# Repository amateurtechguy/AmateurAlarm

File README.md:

# AmateurAlarm
A 4 key alarm clock that is powered by a XIAO ESP32 module, and displayed by a 2.25inch TFT Screen. It has a black screen and red numbers, because that's the amateur tech guy's favorite color scheme!

## What is This?
It is a custom alarm clock powered by a Seeed XIAO ESP32 microcontroller and Arduino Firmware, allowing it to be fully customizable and compact.

Have you ever felt like all you need is a simple, cheap, easy to make alarm clock but, you're simply just irritated from having to click so many buttons and learn so many skills just to make that happen?

Well AmateurAlarm is for you! Cause with AmateurAlarm you can just use the keys in the back to set your alarm whenever you want and the real kicker is that this alarm and it's keys are fully customizeable! so if you're unhappy with what your keys do, just simply hack the firmware and flash it!

## Features:

- 4 key buttons to help set your alarm up
- One buzzer to wake you up!
- Custom PCB to eliminate the need for messy wires
- A 3D printed Case for accessibility and ease
- Custom Arduino Firmware which allows easy reprogramming

### The PCB 

### The schematic

### The 3D Model

#### Made With Kicad!

## How To Use:

Download Arduino IDE on laptop or pc.

then click [here](https://wiki.seeedstudio.com/XIAO_ESP32C3_Getting_Started/) for detailed instructions on how to flash it!

## What I Learned:
- How to design start to finish my own alarm clock
- How alarm clocks work
- How easy it is to understand it
- How C++ works
  
---
## Creator:
made by the amateur tech guy:D

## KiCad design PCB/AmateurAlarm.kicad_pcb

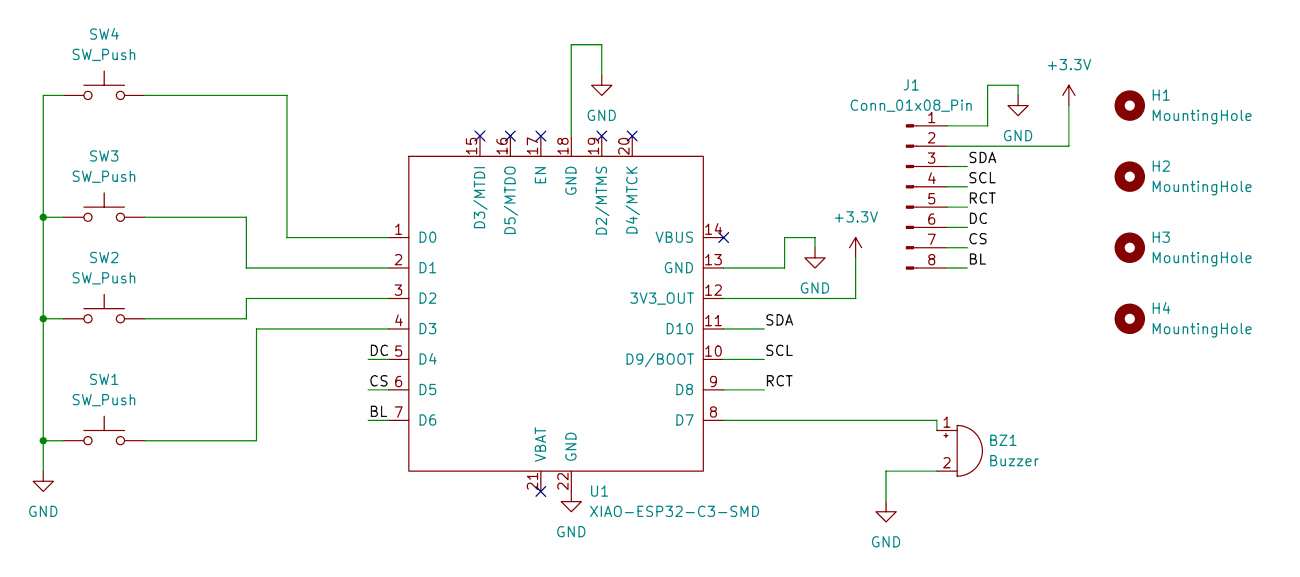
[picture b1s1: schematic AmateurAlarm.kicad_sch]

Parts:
BZ1: Buzzer; Buzzer_12x9.5RM7.6
H1, H2, H3, H4: MountingHole; MountingHole_3.2mm_M3
J1: Conn_01x08_Pin; PinSocket_1x08_P2.54mm_Vertical
SW1, SW2, SW3, SW4: SW_Push; SW_Cherry_MX_1.00u_PCB
U1: XIAO-ESP32-C3-SMD

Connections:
+3.3V: J1.2, U1.12 (3V3_OUT)
/BL: J1.8, U1.7 (D6)
/CS: J1.7, U1.6 (D5)
/DC: J1.6, U1.5 (D4)
/RCT: J1.5, U1.9 (D8)
/SCL: J1.4, U1.10 (D9/BOOT)
/SDA: J1.3, U1.11 (D10)
GND: BZ1.2 (-), J1.1, SW1.1, SW2.1, SW3.1, SW4.1, U1.13 (GND), U1.18 (GND), U1.22 (GND)
unnamed: BZ1.1 (+), U1.8 (D7)
unnamed: SW4.2, U1.1 (D0)
unnamed: SW3.2, U1.2 (D1)
unnamed: SW2.2, U1.3 (D2)
unnamed: SW1.2, U1.4 (D3)

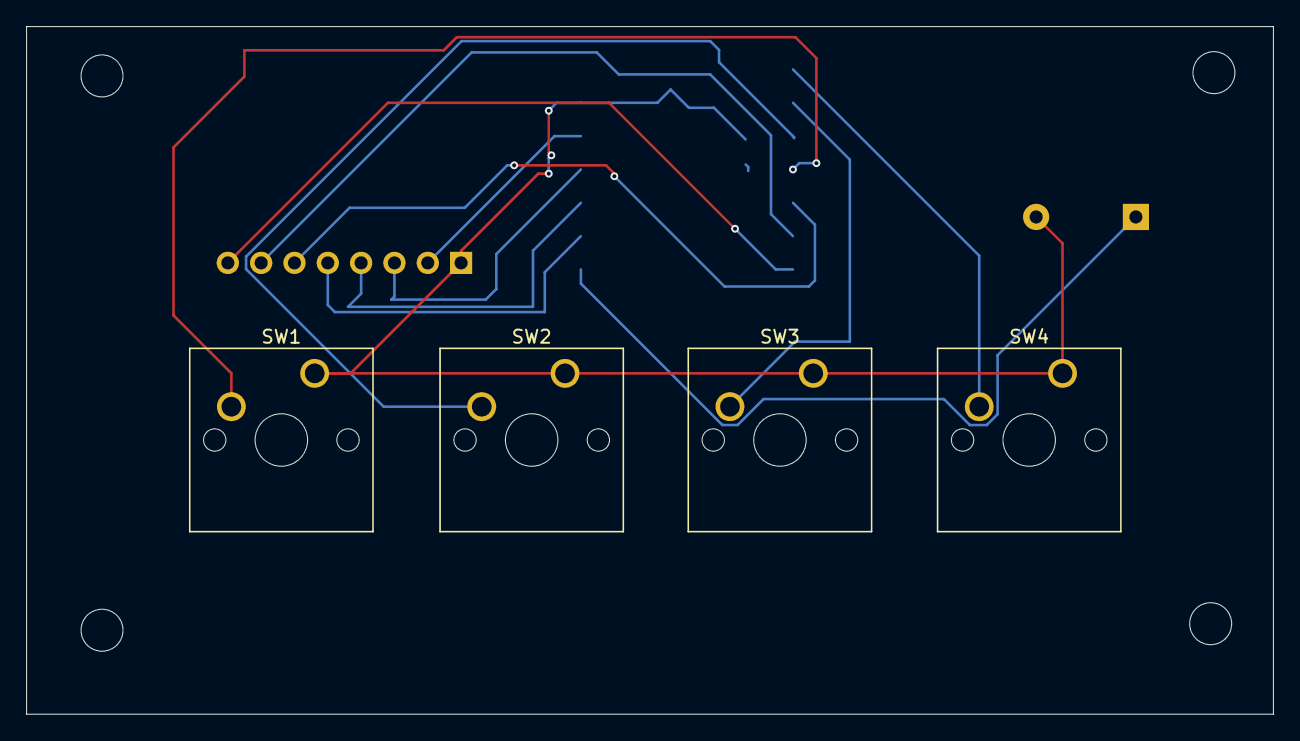
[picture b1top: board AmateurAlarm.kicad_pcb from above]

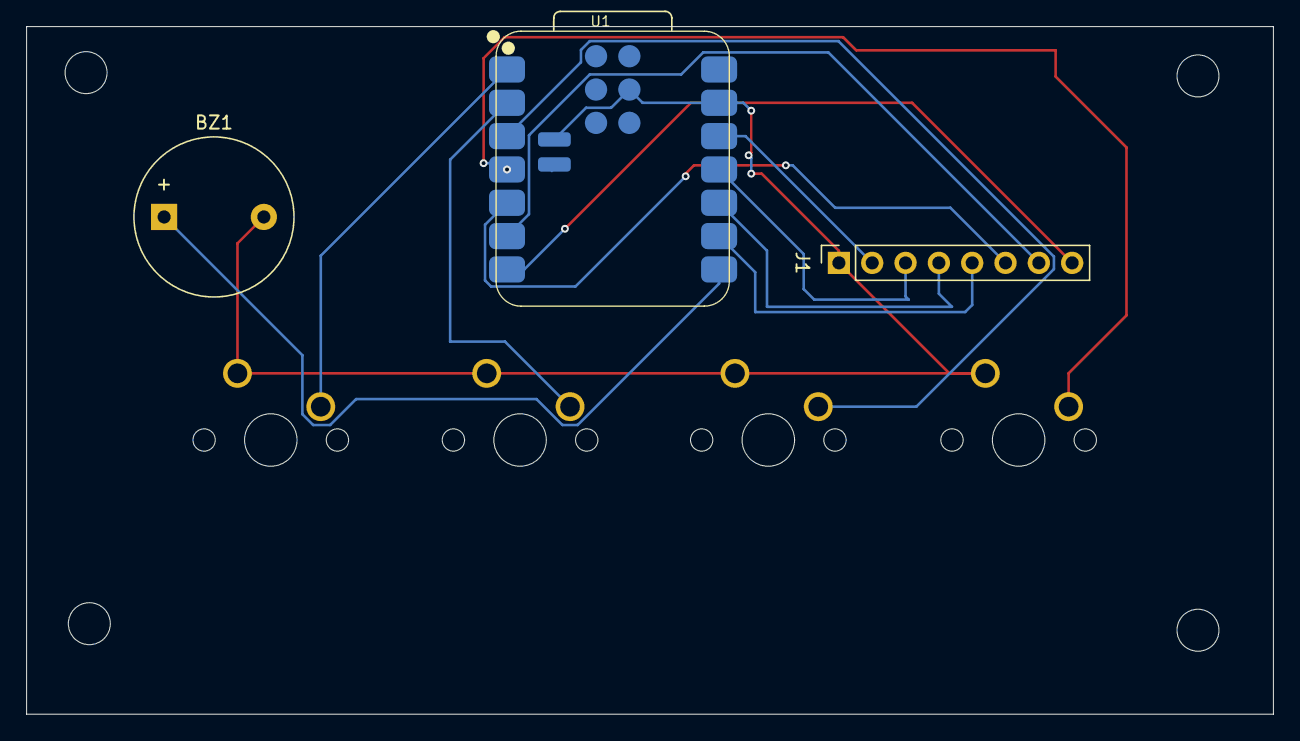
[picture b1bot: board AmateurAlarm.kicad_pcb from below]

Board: 2 copper layers, 95.0 x 52.4 mm, 11 parts (3 on the bottom side), 13 nets.
